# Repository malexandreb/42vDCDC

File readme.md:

created by MAB on 2023-07-06
# 42V down to 5V DC/DC converter

Simple DC/DC converter designed to Step down the voltage from
e-bike power pack (10S) to 5V for use by microcontoller

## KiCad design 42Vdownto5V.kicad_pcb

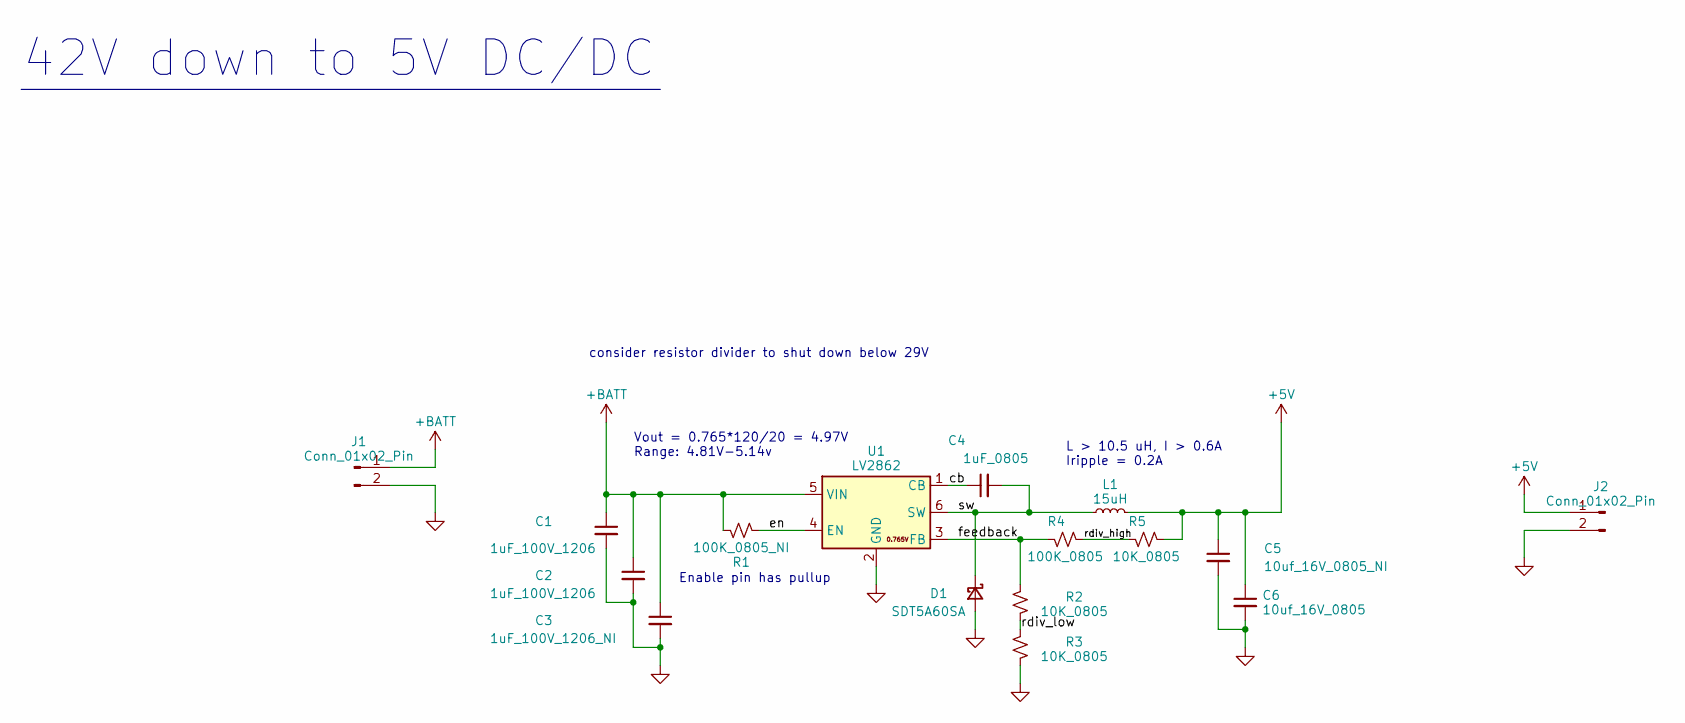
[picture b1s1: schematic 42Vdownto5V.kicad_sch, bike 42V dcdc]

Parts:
C1, C2: 1uF_100V_1206; C_0805_2012Metric_Pad1.18x1.45mm_HandSolder
C3: 1uF_100V_1206_NI; C_0805_2012Metric_Pad1.18x1.45mm_HandSolder
C4: 1uF_0805; C_0805_2012Metric_Pad1.18x1.45mm_HandSolder
C5: 10uf_16V_0805_NI; C_0805_2012Metric_Pad1.18x1.45mm_HandSolder
C6: 10uf_16V_0805; C_0805_2012Metric_Pad1.18x1.45mm_HandSolder
D1: SDT5A60SA; D_SMA_Handsoldering
J1, J2: Conn_01x02_Pin; PinHeader_1x02_P2.54mm_Vertical
L1: 15uH; L_Taiyo-Yuden_MD-5050
R1: 100K_0805_NI; R_0805_2012Metric_Pad1.20x1.40mm_HandSolder
R2, R3, R5: 10K_0805; R_0805_2012Metric_Pad1.20x1.40mm_HandSolder
R4: 100K_0805; R_0805_2012Metric_Pad1.20x1.40mm_HandSolder
U1: LV2862; SOT-23-6

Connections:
+5V: C5.1, C6.1, J2.1, L1.2, R5.1
+BATT: C1.1, C2.1, C3.1, J1.1, R1.2, U1.5 (VIN)
/cb: C4.1, U1.1 (CB)
/en: R1.1, U1.4 (EN)
/feedback: R2.1, R4.2, U1.3 (FB)
/rdiv_high: R4.1, R5.2
/rdiv_low: R2.2, R3.1
/sw: C4.2, D1.1 (K), L1.1, U1.6 (SW)
GND: C1.2, C2.2, C3.2, C5.2, C6.2, D1.2 (A), J1.2, J2.2, R3.2, U1.2 (GND)

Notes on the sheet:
Enable pin has pullup
consider resistor divider to shut down below 29V
42V down to 5V DC/DC
Vout = 0.765*120/20 = 4.97V Range: 4.81V-5.14v
L > 10.5 uH, I > 0.6A Iripple = 0.2A

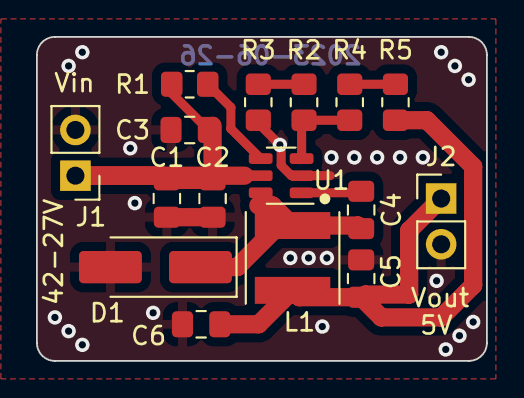
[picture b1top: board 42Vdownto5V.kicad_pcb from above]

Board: 2 copper layers, 25.0 x 18.0 mm, 16 parts (0 on the bottom side), 9 nets.

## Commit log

2023-07-06 board complete and ordered
